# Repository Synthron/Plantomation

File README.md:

# Plantomation
Automatic Plant Watering System with ESP32

## V1
Capable of handling 4 channels simultaneously with one pump

## V2
Capable of handling 12 channels simultaneously with two pumps

---
**WORK IN PROGRESS**

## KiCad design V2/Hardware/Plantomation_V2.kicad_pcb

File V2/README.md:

# Plantomation

DIY plant watering system based on ESP32-S3-WROVER

## Features

- up to 12 channels simultaneously
- water spill detection
- Ambient Temperature and Humidity Sensor
- two pumps for all channels, selected via valves
  - Water pump
  - fertilizer pump
- simple Web-Interface for quick overview and configuration
- SD-Card for local wifi config and logging

## ToDos

- Documentation
  - [ ] Config Explanation
  - [ ] Wifi Management Explanation
  - [ ] UI Explanation
  - [ ] Control Modes Explanation
  - [ ] General Mode of Operation Explanation
- PCB
  - [x] Finish Design
  - [ ] Order
  - [ ] Assemble
  - [ ] Test
- Firmware
  - Frontend
    - [ ] Ajax working
    - [ ] Multi-Page working
    - [ ] Main-Page with all necessary information
    - [ ] Config page
    - [ ] About page
  - Backend
    - [ ] Wifi Management
    - [ ] File Management
      - [ ] SPIFFS
      - [ ] SD Card (preferred if available)
      - [ ] Copy config from SD to SPIFFS
    - [ ] Implement Setup via Webpage
      - [ ] Channels
      - [ ] WiFi
      - [ ] General Config
      - [ ] Debug
      - [ ] Sensor calibration
    - [ ] Objects for channels
    - [ ] Config object
    - [ ] Wifi object
    - [ ] implement sensor read
    - [ ] implement spill detection
    - [ ] implement Moisture Control
    - [ ] implement Time Control (timers)
    - [ ] implement internal water volume counter
    - [ ] implement low-water-alarm
    - [ ] Debug-Levels
    - [ ] Log-Levels

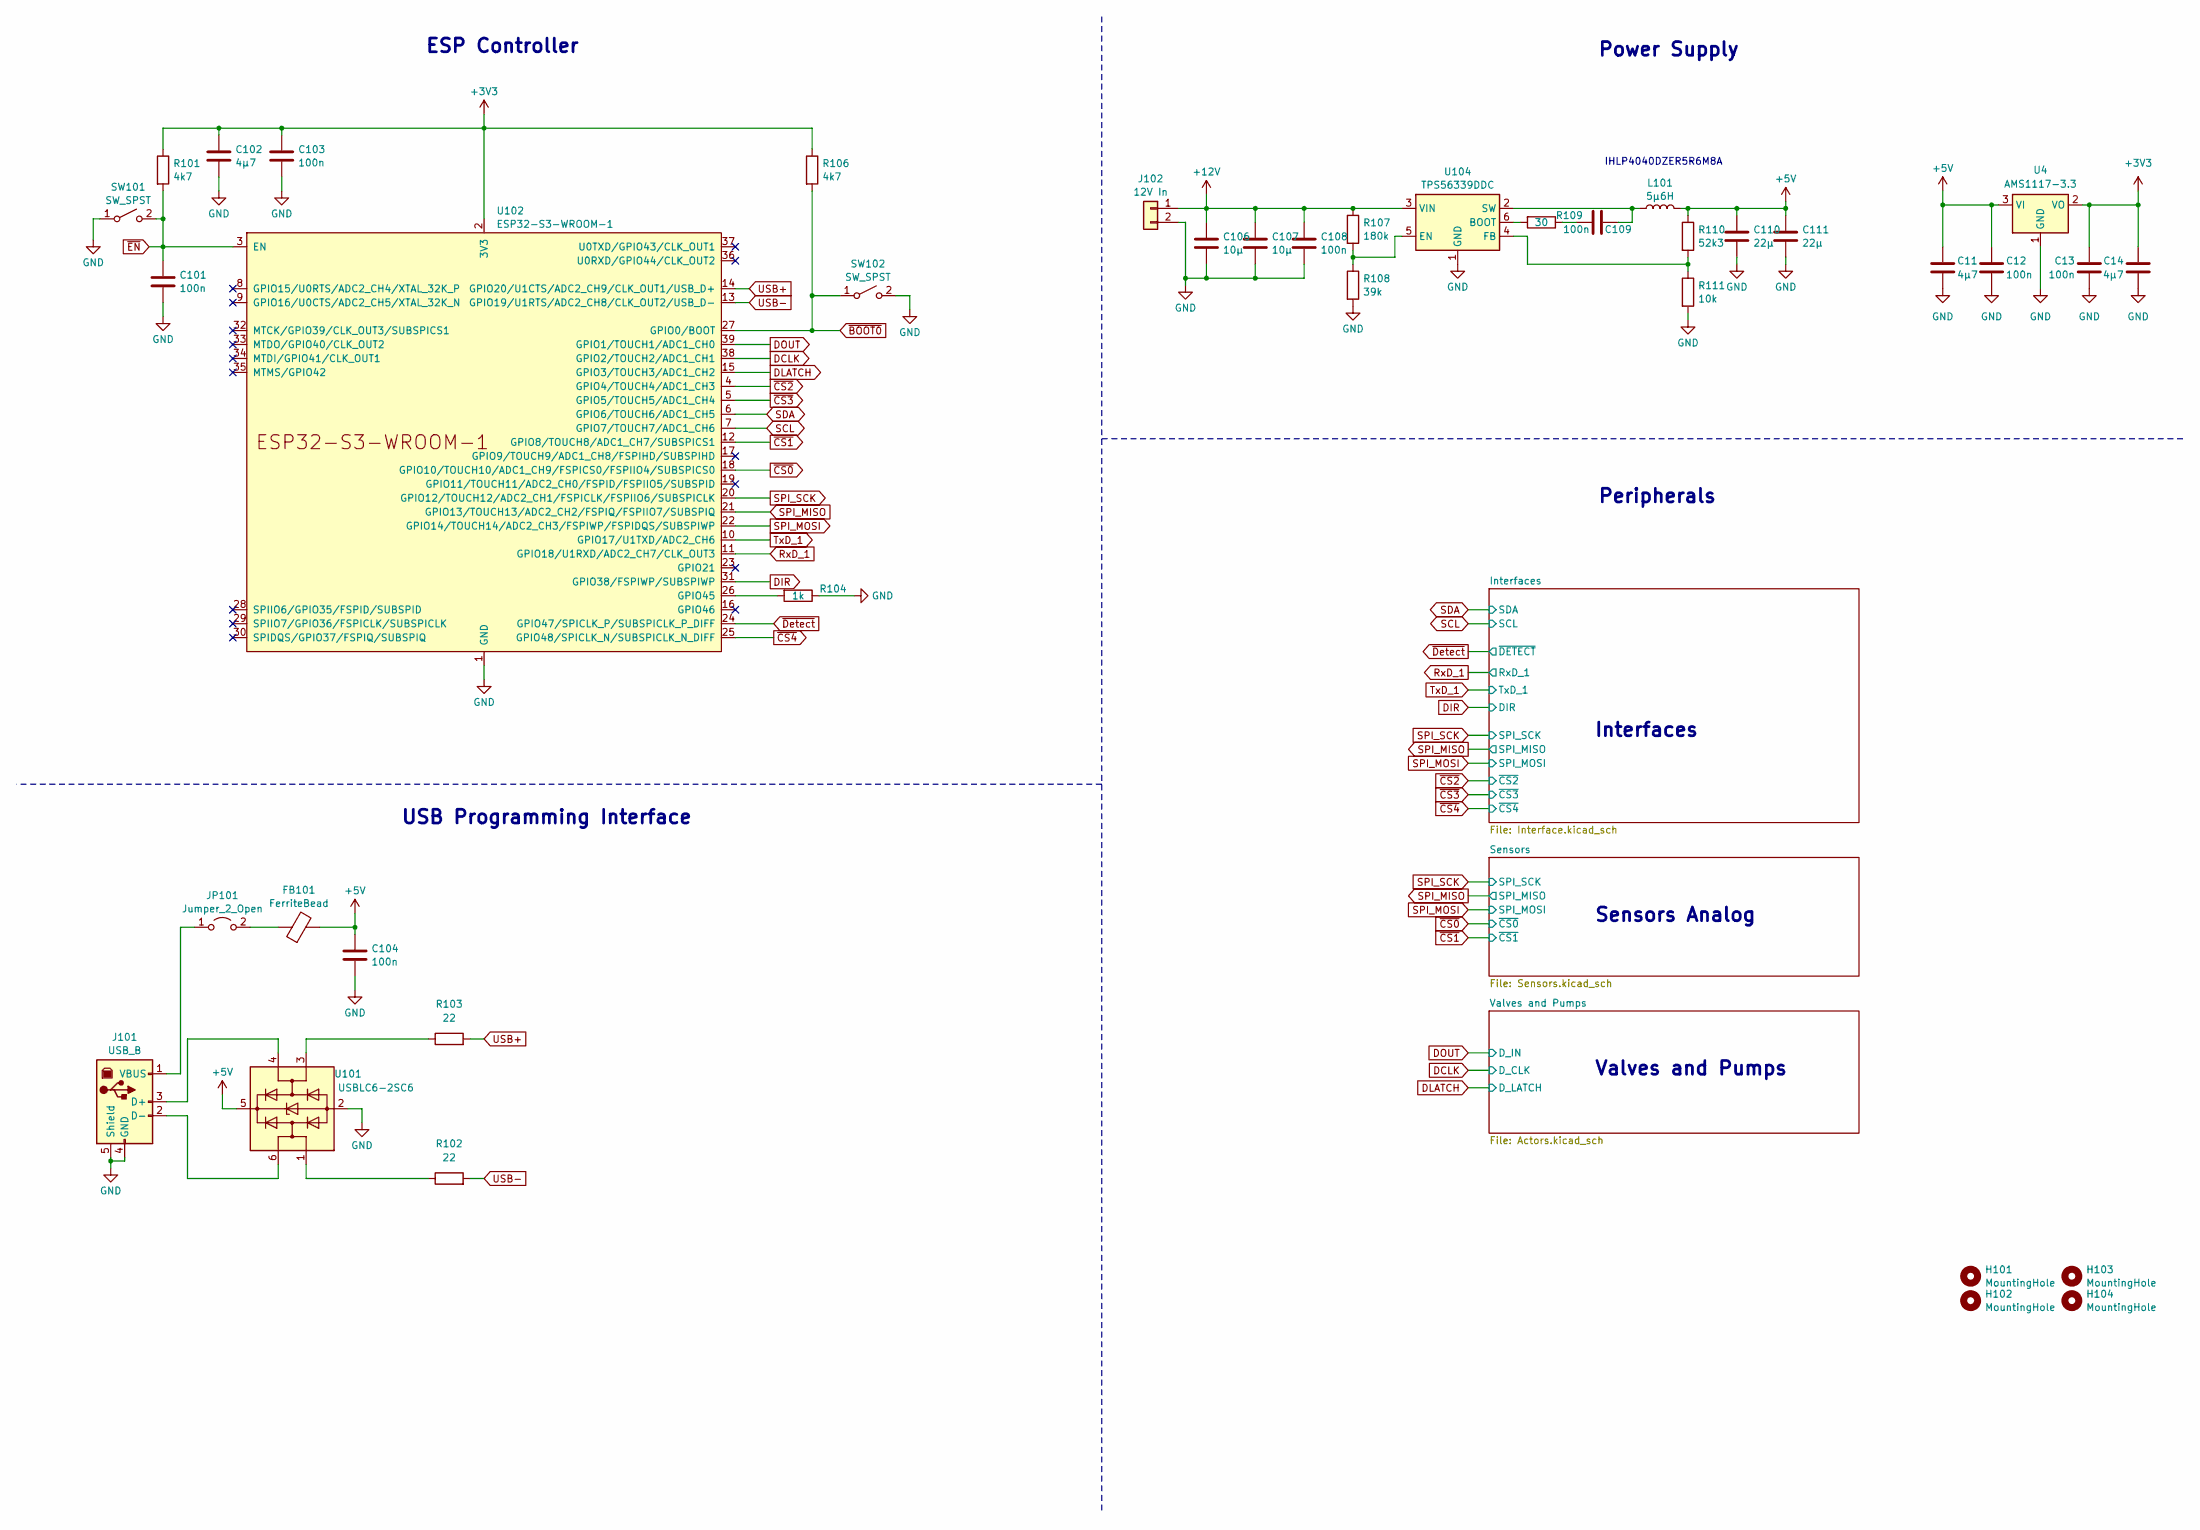
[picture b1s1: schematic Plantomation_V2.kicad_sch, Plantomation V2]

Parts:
C11, C14, C102: 4µ7; C_0805_2012Metric
C12, C13, C101, C103, C104, C108, C109: 100n; C_0805_2012Metric
C106, C107: 10µ; C_0805_2012Metric
C110, C111: 22µ; C_0805_2012Metric
FB101: FerriteBead; SMB-001
H101, H102, H103, H104: MountingHole; MountingHole_3.2mm_M3
J101: USB_B; USB_B_Lumberg_2411_02_Horizontal
J102: 12V In; JST_XH_B2B-XH-A_1x02_P2.50mm_Vertical
JP101: Jumper_2_Open; SolderJumper-2_P1.3mm_Open_TrianglePad1.0x1.5mm
L101: 5µ6H; L_Vishay_IHLP-4040
R101, R106: 4k7; R_0805_2012Metric
R102, R103: 22; R_0805_2012Metric
R104: 1k; R_0805_2012Metric
R107: 180k; R_0805_2012Metric
R108: 39k; R_0805_2012Metric
R109: 30; R_0805_2012Metric
R110: 52k3; R_0805_2012Metric
R111: 10k; R_0805_2012Metric
SW101, SW102: SW_SPST; SW_Tactile_SPST_NO_Straight_CK_PTS636Sx25SMTRLFS
U4: AMS1117-3.3; SOT-223-3_TabPin2
U101: USBLC6-2SC6; SOT-23-6
U102: ESP32-S3-WROOM-1
U104: TPS56339DDC; SOT-23-6

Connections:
+3V3: C102.1, C103.1, R101.1, R106.1, U102.2 (3V3); also elsewhere on the board
+5V: C104.1, C110.1, C111.1, FB101.2, L101.2, R110.1, U101.5 (VBUS); also elsewhere on the board
+12V: C106.1, C107.1, C108.1, J102.1, R107.1, U104.3 (VIN); also elsewhere on the board
DCLK: U102.38 (GPIO2/TOUCH2/ADC1_CH1); also elsewhere on the board
DIR: U102.31 (GPIO38/FSPIWP/SUBSPIWP)
DLATCH: U102.15 (GPIO3/TOUCH3/ADC1_CH2); also elsewhere on the board
DOUT: U102.39 (GPIO1/TOUCH1/ADC1_CH0); also elsewhere on the board
GND: C101.2, C102.2, C103.2, C104.2, C106.2, C107.2, C108.2, C110.2, C111.2, J101.4 (GND), J101.5 (Shield), J102.2, R104.1, R108.2, R111.2, SW101.1 (A), SW102.2 (B), U101.2 (GND), U102.1 (GND), U102.40 (GND), U102.41 (GND), U104.1 (GND); also elsewhere on the board
unnamed: C109.1, R109.1
unnamed: J101.3 (D+), U101.4 (I/O2)
unnamed: J101.2 (D-), U101.6 (I/O1)
unnamed: J101.1 (VBUS), JP101.1 (A)
unnamed: FB101.1, JP101.2 (B)
unnamed: R102.1, U101.1 (I/O1)
unnamed: R103.1, U101.3 (I/O2)
unnamed: R104.2, U102.26 (GPIO45)
unnamed: R109.2, U104.6 (BOOT)
unnamed: R107.2, R108.1, U104.5 (EN)
unnamed: R110.2, R111.1, U104.4 (FB)
unnamed: C109.2, L101.1, U104.2 (SW)
RxD_1: U102.11 (GPIO18/U1RXD/ADC2_CH7/CLK_OUT3)
SCL: U102.7 (GPIO7/TOUCH7/ADC1_CH6); also elsewhere on the board
SDA: U102.6 (GPIO6/TOUCH6/ADC1_CH5); also elsewhere on the board
SPI_MISO: U102.21 (GPIO13/TOUCH13/ADC2_CH2/FSPIQ/FSPIIO7/S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); also elsewhere on the board
SPI_MOSI: U102.22 (GPIO14/TOUCH14/ADC2_CH3/FSPIWP/FSPIDQS/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); also elsewhere on the board
SPI_SCK: U102.20 (GPIO12/TOUCH12/ADC2_CH1/FSPICLK/FSPIIO6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); also elsewhere on the board
TxD_1: U102.10 (GPIO17/U1TXD/ADC2_CH6)
USB+: R103.2, U102.14 (GPIO20/U1CTS/ADC2_CH9/CLK_OUT1/USB_D+)
USB-: R102.2, U102.13 (GPIO19/U1RTS/ADC2_CH8/CLK_OUT2/USB_D-)
~BOOT0: R106.2, SW102.1 (A), U102.27 (GPIO0/BOOT)
~CS0: U102.18 (GPIO10/TOUCH10/ADC1_CH9/FSPICS0/FSPIIO4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); also elsewhere on the board
~CS1: U102.12 (GPIO8/TOUCH8/ADC1_CH7/SUBSPICS1); also elsewhere on the board
~CS2: U102.4 (GPIO4/TOUCH4/ADC1_CH3); also elsewhere on the board
~CS3: U102.5 (GPIO5/TOUCH5/ADC1_CH4); also elsewhere on the board
~CS4: U102.25 (GPIO48/SPICLK_N/SUBSPICLK_N_DIFF); also elsewhere on the board
~Detect: U102.24 (GPIO47/SPICLK_P/SUBSPICLK_P_DIFF); also elsewhere on the board
~EN: C101.1, R101.2, SW101.2 (B), U102.3 (EN)

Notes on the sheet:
Valves and Pumps
IHLP4040DZER5R6M8A
Interfaces
Sensors Analog
Peripherals
Power Supply
ESP Controller
USB Programming Interface

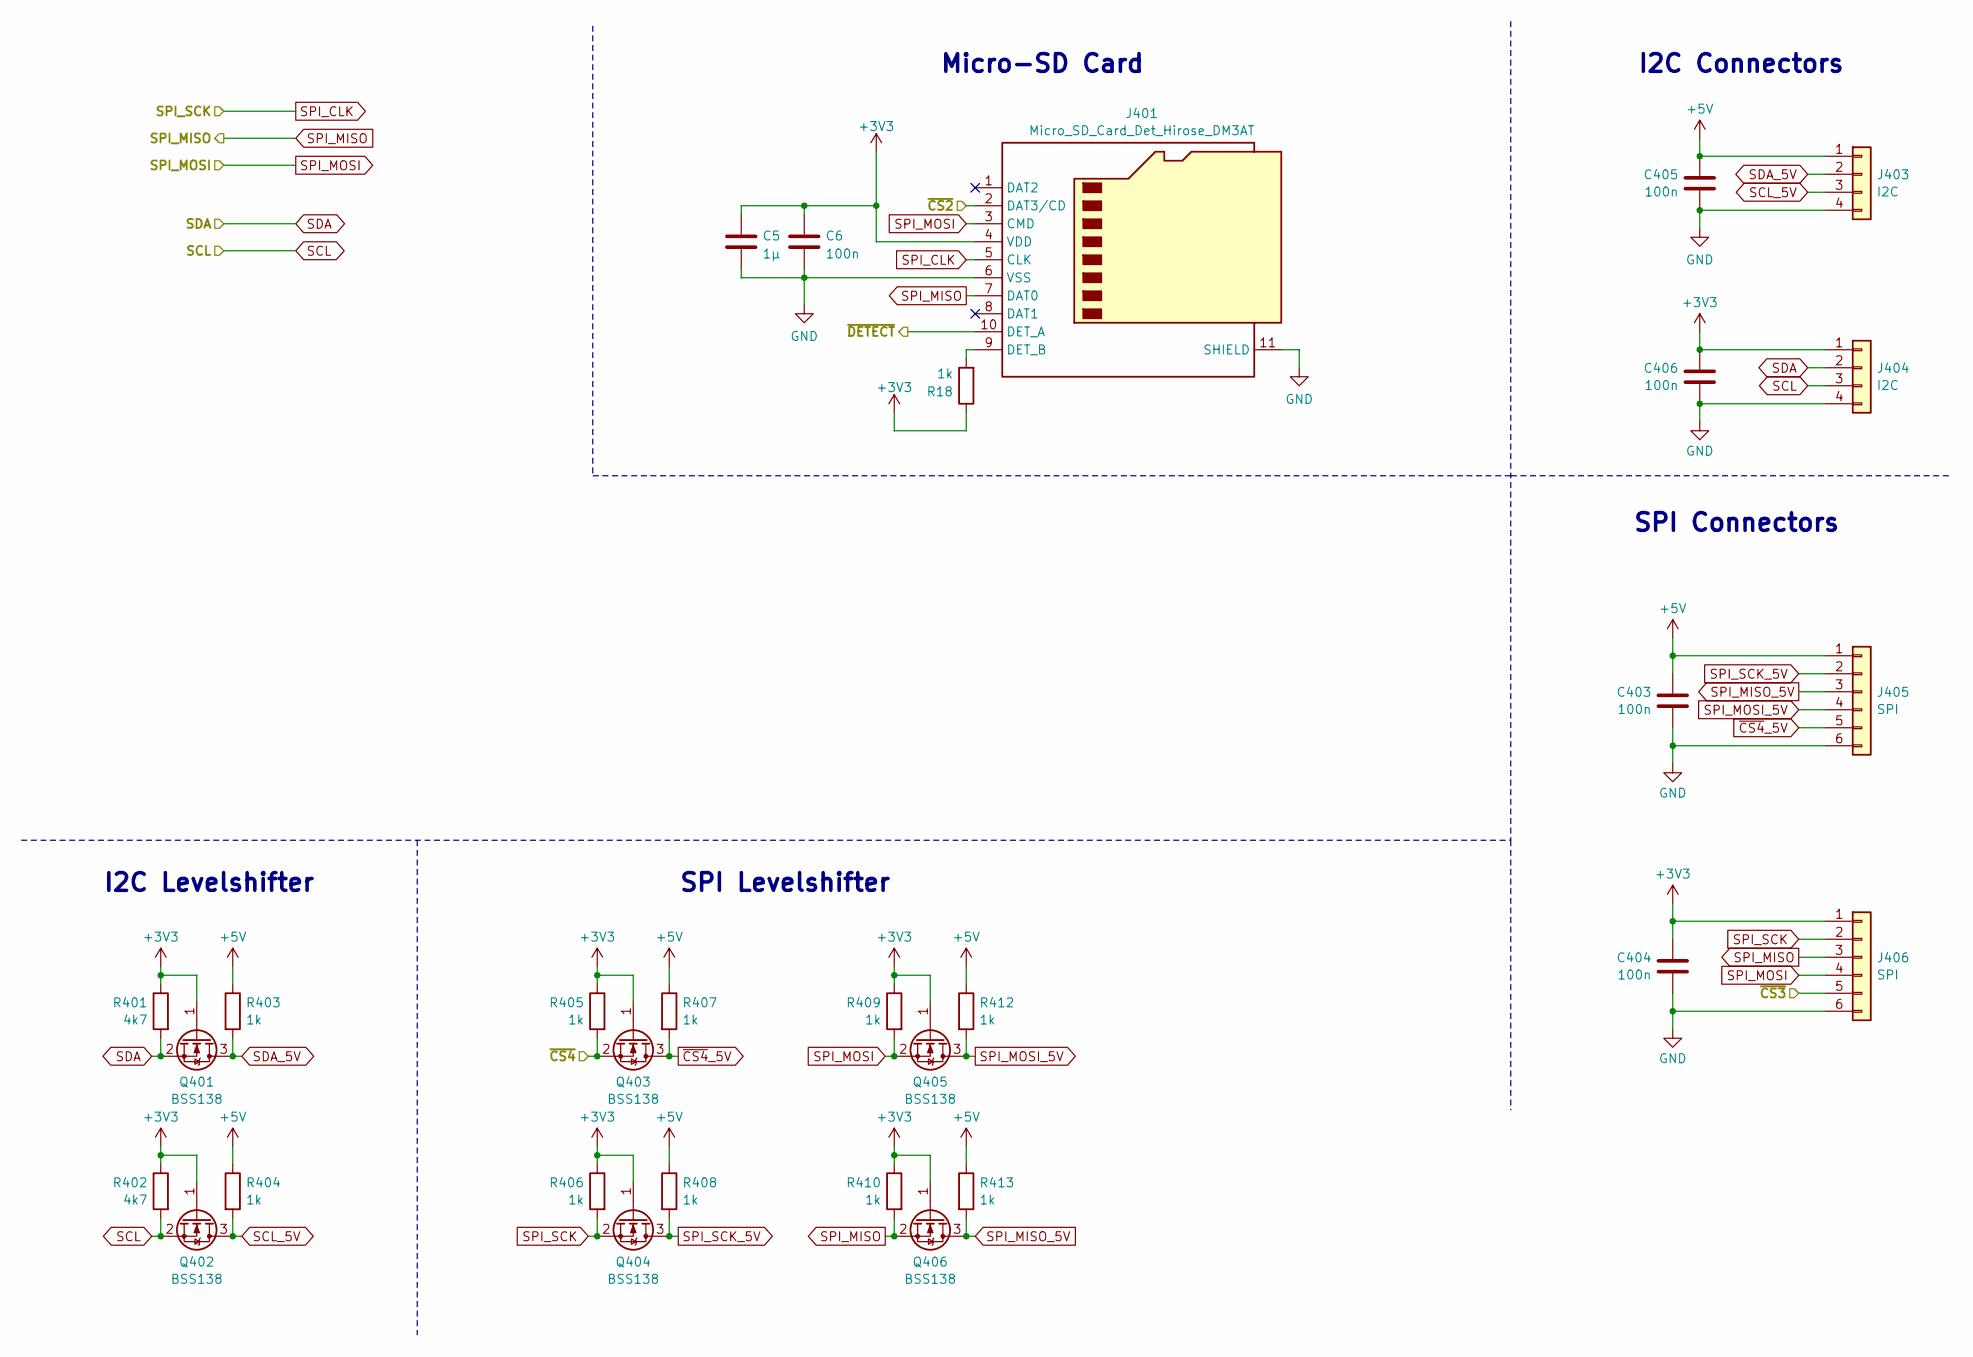
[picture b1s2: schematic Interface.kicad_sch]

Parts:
C5: 1µ; C_0805_2012Metric
C6, C403, C404, C405, C406: 100n; C_0805_2012Metric
J401: Micro_SD_Card_Det_Hirose_DM3AT; microSD_HC_Hirose_DM3AT-SF-PEJM5
J403, J404: I2C; PinHeader_1x04_P2.54mm_Vertical
J405, J406: SPI; PinHeader_1x06_P2.54mm_Vertical
Q401, Q402, Q403, Q404, Q405, Q406: BSS138; SOT-23
R18, R403, R404, R405, R406, R407, R408, R409, R410, R412, R413: 1k; R_0805_2012Metric
R401, R402: 4k7; R_0805_2012Metric

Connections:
+3V3: C404.1, C406.1, J401.4 (VDD), J404.1, J406.1, Q401.1 (G), Q402.1 (G), Q403.1 (G), Q404.1 (G), Q405.1 (G), Q406.1 (G), R401.1, R402.1, R405.1, R406.1, R409.1, R410.1; also elsewhere on the board
+5V: C403.1, C405.1, J403.1, J405.1, R403.1, R404.1, R407.1, R408.1, R412.1, R413.1; also elsewhere on the board
GND: C403.2, C404.2, C405.2, C406.2, J401.6 (VSS), J401.11 (SHIELD), J403.4, J404.4, J405.6, J406.6; also elsewhere on the board
unnamed 51: J401.9 (DET_B); also elsewhere on the board
SCL: J404.3, Q402.2 (S), R402.2; also elsewhere on the board
SCL_5V: J403.3, Q402.3 (D), R404.2
SDA: J404.2, Q401.2 (S), R401.2; also elsewhere on the board
SDA_5V: J403.2, Q401.3 (D), R403.2
SPI_MISO: J401.7 (DAT0), J406.3, Q406.2 (S), R410.2; also elsewhere on the board
SPI_MISO_5V: J405.3, Q406.3 (D), R413.2
SPI_MOSI: J401.3 (CMD), J406.4, Q405.2 (S), R409.2; also elsewhere on the board
SPI_MOSI_5V: J405.4, Q405.3 (D), R412.2
SPI_SCK: J401.5 (CLK), J406.2, Q404.2 (S), R406.2; also elsewhere on the board
SPI_SCK_5V: J405.2, Q404.3 (D), R408.2
~CS2: J401.2 (DAT3/CD); also elsewhere on the board
~CS3: J406.5; also elsewhere on the board
~CS4: Q403.2 (S), R405.2; also elsewhere on the board
~CS4_5V: J405.5, Q403.3 (D), R407.2
~Detect: J401.10 (DET_A); also elsewhere on the board

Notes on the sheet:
I2C Connectors
SPI Levelshifter
Micro-SD Card
SPI Connectors
I2C Levelshifter

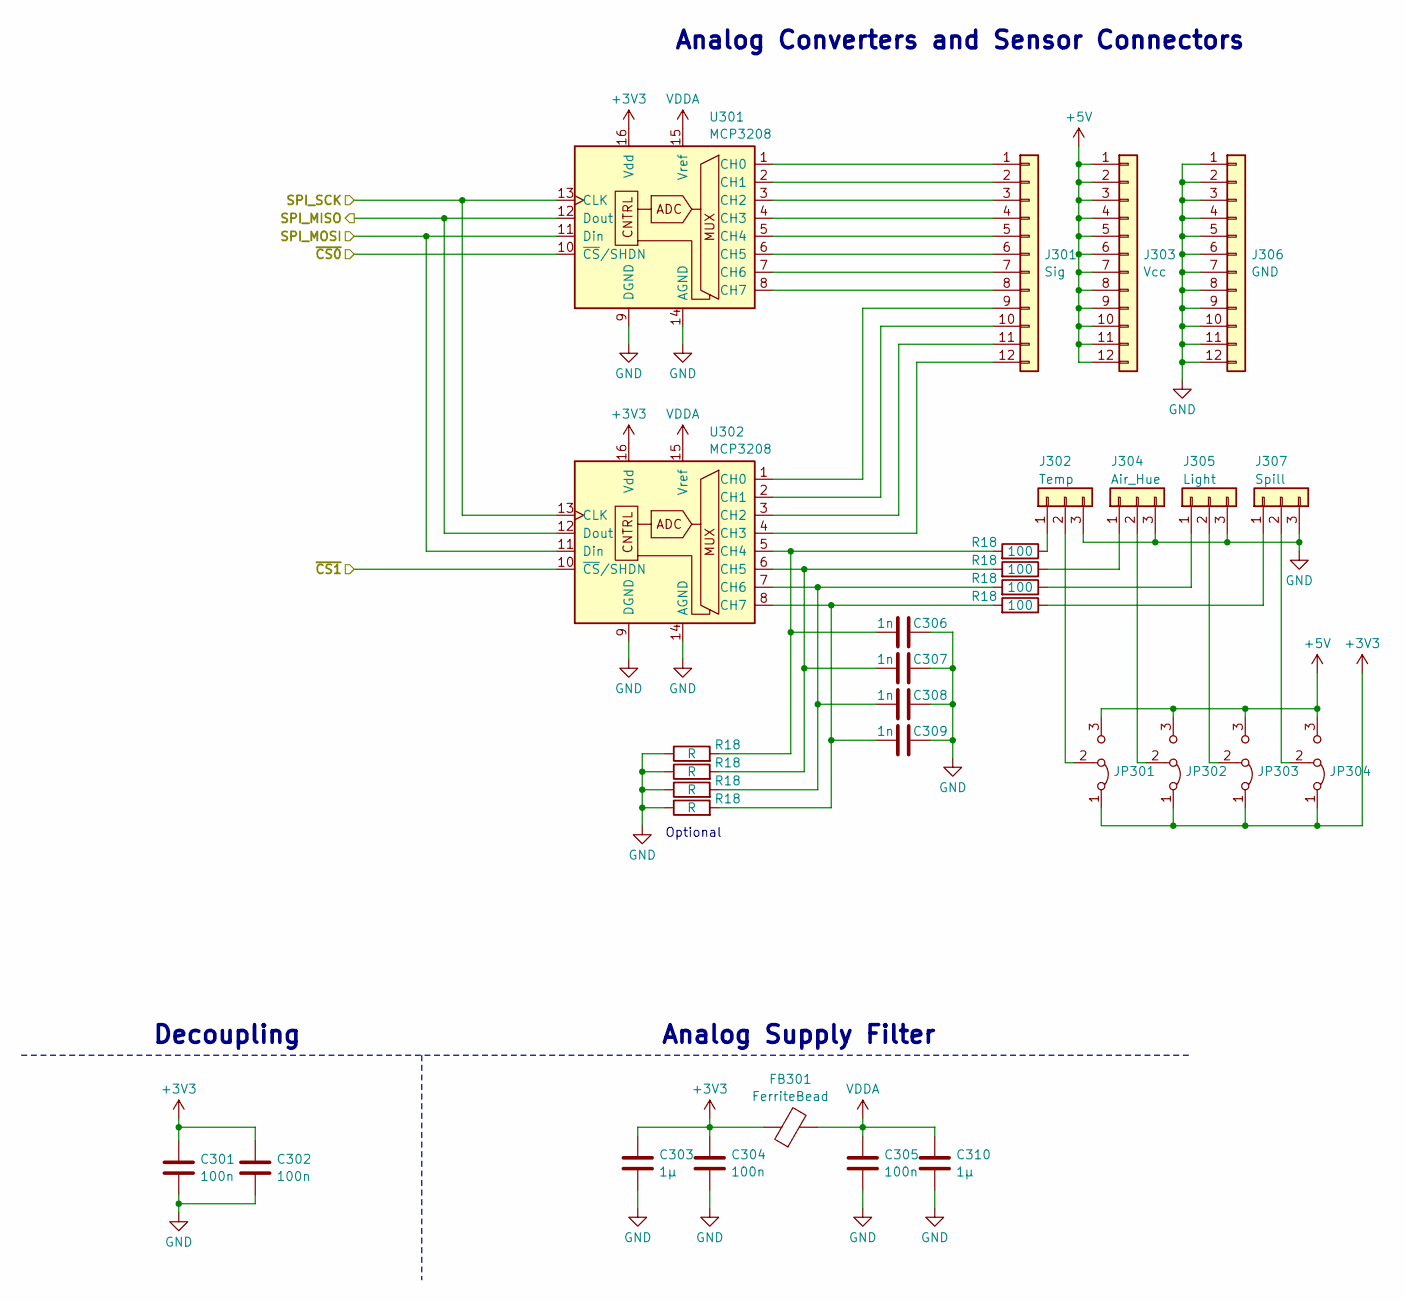
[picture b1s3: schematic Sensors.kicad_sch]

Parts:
C301, C302, C304, C305: 100n; C_0805_2012Metric
C303, C310: 1µ; C_0805_2012Metric
C306, C307, C308, C309: 1n; C_0805_2012Metric
FB301: FerriteBead; SMB-001
J301: Sig; PinHeader_1x12_P2.54mm_Vertical
J302: Temp; PinHeader_1x03_P2.54mm_Vertical
J303: Vcc; PinHeader_1x12_P2.54mm_Vertical
J304: Air_Hue; PinHeader_1x03_P2.54mm_Vertical
J305: Light; PinHeader_1x03_P2.54mm_Vertical
J306: GND; PinHeader_1x12_P2.54mm_Vertical
J307: Spill; PinHeader_1x03_P2.54mm_Vertical
JP301, JP302, JP303, JP304: Jumper_3_Bridged12; SolderJumper-3_P1.3mm_Open_Pad1.0x1.5mm
R18: R; R_0805_2012Metric
U301, U302: MCP3208; SOIC-16_4.55x10.3mm_P1.27mm

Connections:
+3V3: C301.1, C302.1, C303.1, C304.1, FB301.1, JP301.1 (A), JP302.1 (A), JP303.1 (A), JP304.1 (A), U301.16 (Vdd), U302.16 (Vdd); also elsewhere on the board
+5V: J303.1, J303.2, J303.3, J303.4, J303.5, J303.6, J303.7, J303.8, J303.9, J303.10, J303.11, J303.12, JP301.3 (B), JP302.3 (B), JP303.3 (B), JP304.3 (B); also elsewhere on the board
GND: C301.2, C302.2, C303.2, C304.2, C305.2, C306.2, C307.2, C308.2, C309.2, C310.2, J302.3, J304.3, J305.3, J306.1, J306.2, J306.3, J306.4, J306.5, J306.6, J306.7, J306.8, J306.9, J306.10, J306.11, J306.12, J307.3, U301.9 (DGND), U301.14 (AGND), U302.9 (DGND), U302.14 (AGND); also elsewhere on the board
unnamed: J301.1, U301.1 (CH0)
unnamed: J301.2, U301.2 (CH1)
unnamed: J301.3, U301.3 (CH2)
unnamed: J301.4, U301.4 (CH3)
unnamed: J301.5, U301.5 (CH4)
unnamed: J301.6, U301.6 (CH5)
unnamed: J301.7, U301.7 (CH6)
unnamed: J301.8, U301.8 (CH7)
unnamed: J301.9, U302.1 (CH0)
unnamed: J301.10, U302.2 (CH1)
unnamed: J301.11, U302.3 (CH2)
unnamed: J301.12, U302.4 (CH3)
unnamed 43: J302.1; also elsewhere on the board
unnamed: J302.2, JP301.2 (C)
unnamed 45: J304.1; also elsewhere on the board
unnamed: J304.2, JP302.2 (C)
unnamed 47: J305.1; also elsewhere on the board
unnamed: J305.2, JP303.2 (C)
unnamed 49: J307.1; also elsewhere on the board
unnamed: J307.2, JP304.2 (C)
unnamed 75: C306.1, U302.5 (CH4); also elsewhere on the board
unnamed 76: C307.1, U302.6 (CH5); also elsewhere on the board
unnamed 77: C308.1, U302.7 (CH6); also elsewhere on the board
unnamed 78: C309.1, U302.8 (CH7); also elsewhere on the board
SPI_MISO: U301.12 (Dout), U302.12 (Dout); also elsewhere on the board
SPI_MOSI: U301.11 (Din), U302.11 (Din); also elsewhere on the board
SPI_SCK: U301.13 (CLK), U302.13 (CLK); also elsewhere on the board
VDDA: C305.1, C310.1, FB301.2, U301.15 (Vref), U302.15 (Vref)
~CS0: U301.10 (~CS/SHDN); also elsewhere on the board
~CS1: U302.10 (~CS/SHDN); also elsewhere on the board

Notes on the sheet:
Analog Converters and Sensor Connectors
Analog Supply Filter
Decoupling
Optional

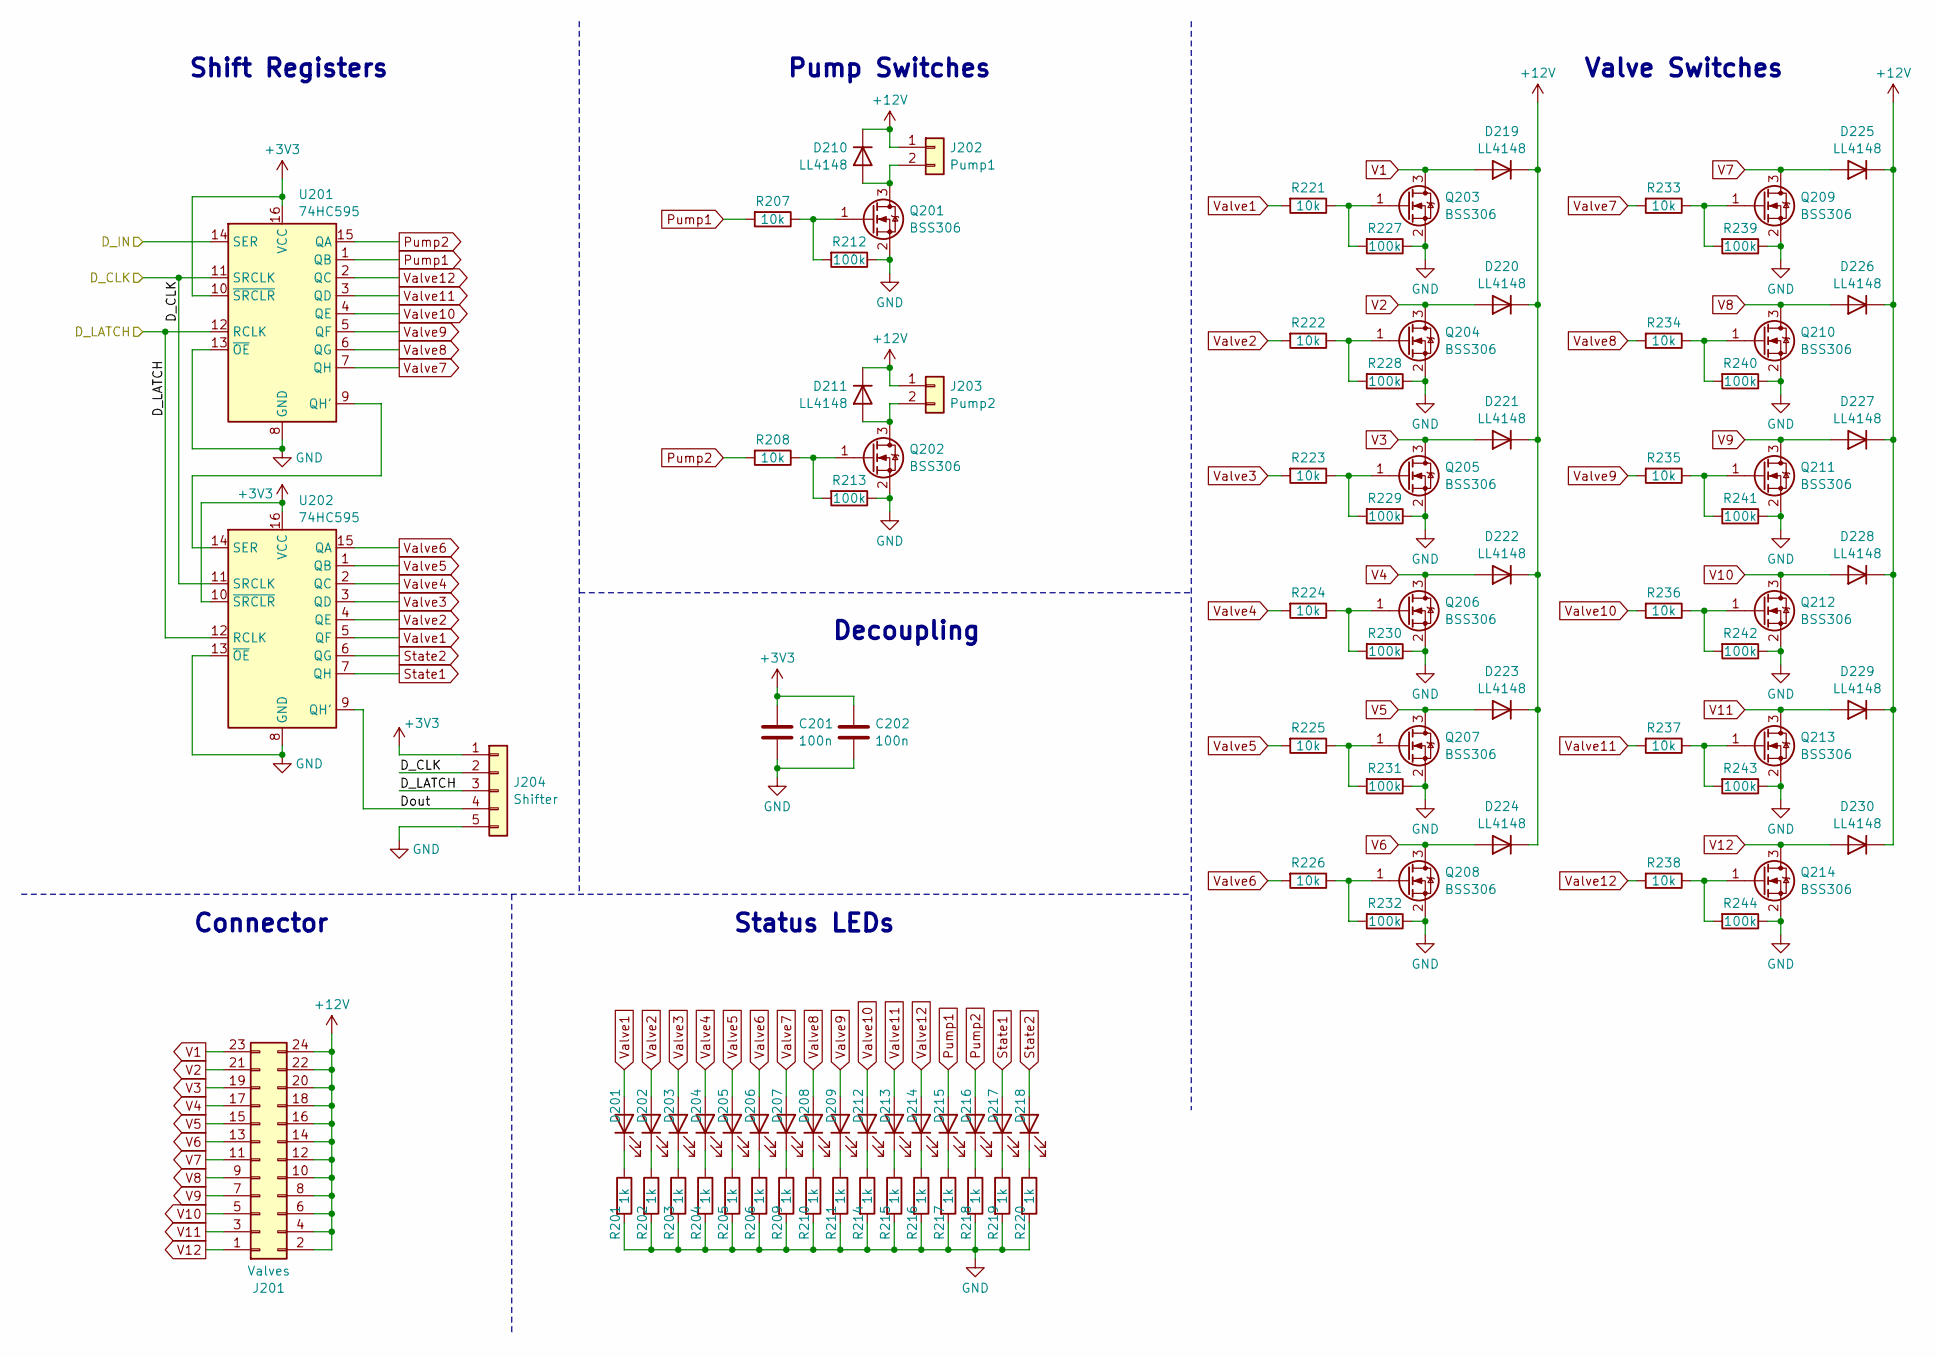
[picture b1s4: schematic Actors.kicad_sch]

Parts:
C201, C202: 100n; C_0805_2012Metric
D201, D202, D203, D204, D205, D206, D207, D208, D209, D212, D213, D214, D215, D216, D217, D218: LED; LED_0805_2012Metric
D210, D211, D219, D220, D221, D222, D223, D224, D225, D226, D227, D228, D229, D230: LL4148; D_MiniMELF
J201: Valves; PinHeader_2x12_P2.54mm_Vertical
J202: Pump1; JST_XH_B2B-XH-A_1x02_P2.50mm_Vertical
J203: Pump2; JST_XH_B2B-XH-A_1x02_P2.50mm_Vertical
J204: Shifter; PinSocket_1x05_P2.54mm_Vertical
Q201, Q202, Q203, Q204, Q205, Q206, Q207, Q208, Q209, Q210, Q211, Q212, Q213, Q214: BSS306; SOT-23-3
R201, R202, R203, R204, R205, R206, R209, R210, R211, R214, R215, R216, R217, R218, R219, R220: 1k; R_0805_2012Metric
R207, R208, R221, R222, R223, R224, R225, R226, R233, R234, R235, R236, R237, R238: 10k; R_0805_2012Metric
R212, R213, R227, R228, R229, R230, R231, R232, R239, R240, R241, R242, R243, R244: 100k; R_0805_2012Metric
U201, U202: 74HC595; SOIC-16_4.55x10.3mm_P1.27mm

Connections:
+3V3: C201.1, C202.1, J204.1, U201.10 (~SRCLR), U201.16 (VCC), U202.10 (~SRCLR), U202.16 (VCC); also elsewhere on the board
+12V: D210.1 (K), D211.1 (K), D219.1 (K), D220.1 (K), D221.1 (K), D222.1 (K), D223.1 (K), D224.1 (K), D225.1 (K), D226.1 (K), D227.1 (K), D228.1 (K), D229.1 (K), D230.1 (K), J201.2, J201.4, J201.6, J201.8, J201.10, J201.12, J201.14, J201.16, J201.18, J201.20, J201.22, J201.24, J202.1, J203.1; also elsewhere on the board
/Valves and Pumps/Dout: J204.4, U202.9 (QH')
DCLK: J204.2, U201.11 (SRCLK), U202.11 (SRCLK); also elsewhere on the board
DLATCH: J204.3, U201.12 (RCLK), U202.12 (RCLK); also elsewhere on the board
DOUT: U201.14 (SER); also elsewhere on the board
GND: C201.2, C202.2, J204.5, Q201.2 (S), Q202.2 (S), Q203.2 (S), Q204.2 (S), Q205.2 (S), Q206.2 (S), Q207.2 (S), Q208.2 (S), Q209.2 (S), Q210.2 (S), Q211.2 (S), Q212.2 (S), Q213.2 (S), Q214.2 (S), R201.2, R202.2, R203.2, R204.2, R205.2, R206.2, R209.2, R210.2, R211.2, R212.1, R213.1, R214.2, R215.2, R216.2, R217.2, R218.2, R219.2, R220.2, R227.1, R228.1, R229.1, R230.1, R231.1, R232.1, R239.1, R240.1, R241.1, R242.1, R243.1, R244.1, U201.8 (GND), U201.13 (~OE), U202.8 (GND), U202.13 (~OE); also elsewhere on the board
unnamed: D201.1 (K), R201.1
unnamed: D202.1 (K), R202.1
unnamed: D203.1 (K), R203.1
unnamed: D204.1 (K), R204.1
unnamed: D205.1 (K), R205.1
unnamed: D206.1 (K), R206.1
unnamed: D207.1 (K), R209.1
unnamed: D208.1 (K), R210.1
unnamed: D209.1 (K), R211.1
unnamed: D210.2 (A), J202.2, Q201.3 (D)
unnamed: D211.2 (A), J203.2, Q202.3 (D)
unnamed: D212.1 (K), R214.1
unnamed: D213.1 (K), R215.1
unnamed: D214.1 (K), R216.1
unnamed: D215.1 (K), R217.1
unnamed: D216.1 (K), R218.1
unnamed: D217.1 (K), R219.1
unnamed: D218.1 (K), R220.1
unnamed: Q201.1 (G), R207.1, R212.2
unnamed: Q202.1 (G), R208.1, R213.2
unnamed: Q203.1 (G), R221.1, R227.2
unnamed: Q204.1 (G), R222.1, R228.2
unnamed: Q205.1 (G), R223.1, R229.2
unnamed: Q206.1 (G), R224.1, R230.2
unnamed: Q207.1 (G), R225.1, R231.2
unnamed: Q208.1 (G), R226.1, R232.2
unnamed: Q209.1 (G), R233.1, R239.2
unnamed: Q210.1 (G), R234.1, R240.2
unnamed: Q211.1 (G), R235.1, R241.2
unnamed: Q212.1 (G), R236.1, R242.2
unnamed: Q213.1 (G), R237.1, R243.2
unnamed: Q214.1 (G), R238.1, R244.2
unnamed: U201.9 (QH'), U202.14 (SER)
Pump1: D215.2 (A), R207.2, U201.1 (QB)
Pump2: D216.2 (A), R208.2, U201.15 (QA)
State1: D217.2 (A), U202.7 (QH)
State2: D218.2 (A), U202.6 (QG)
V1: D219.2 (A), J201.23, Q203.3 (D)
V2: D220.2 (A), J201.21, Q204.3 (D)
V3: D221.2 (A), J201.19, Q205.3 (D)
V4: D222.2 (A), J201.17, Q206.3 (D)
V5: D223.2 (A), J201.15, Q207.3 (D)
V6: D224.2 (A), J201.13, Q208.3 (D)
V7: D225.2 (A), J201.11, Q209.3 (D)
V8: D226.2 (A), J201.9, Q210.3 (D)
V9: D227.2 (A), J201.7, Q211.3 (D)
V10: D228.2 (A), J201.5, Q212.3 (D)
V11: D229.2 (A), J201.3, Q213.3 (D)
V12: D230.2 (A), J201.1, Q214.3 (D)
Valve1: D201.2 (A), R221.2, U202.5 (QF)
Valve2: D202.2 (A), R222.2, U202.4 (QE)
Valve3: D203.2 (A), R223.2, U202.3 (QD)
Valve4: D204.2 (A), R224.2, U202.2 (QC)
Valve5: D205.2 (A), R225.2, U202.1 (QB)
Valve6: D206.2 (A), R226.2, U202.15 (QA)
Valve7: D207.2 (A), R233.2, U201.7 (QH)
Valve8: D208.2 (A), R234.2, U201.6 (QG)
Valve9: D209.2 (A), R235.2, U201.5 (QF)
Valve10: D212.2 (A), R236.2, U201.4 (QE)
Valve11: D213.2 (A), R237.2, U201.3 (QD)
Valve12: D214.2 (A), R238.2, U201.2 (QC)

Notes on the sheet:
Valve Switches
Connector
Pump Switches
Status LEDs
Shift Registers
Decoupling

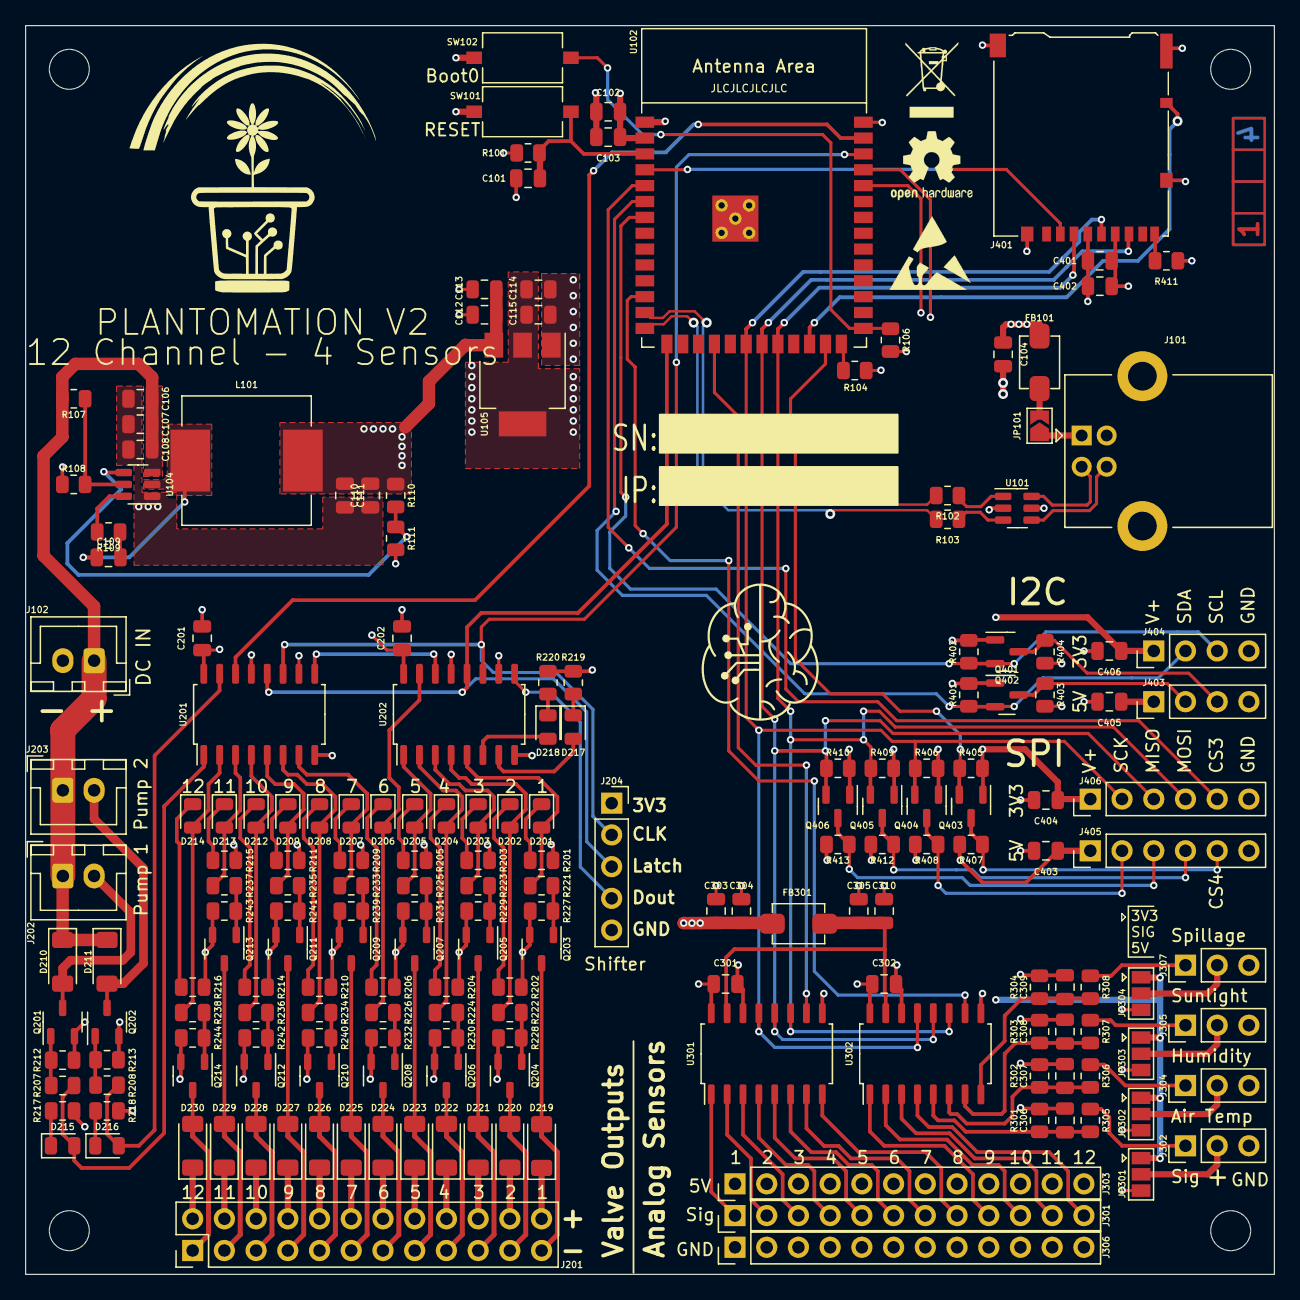
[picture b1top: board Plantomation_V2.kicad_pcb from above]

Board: 4 copper layers, 100.0 x 100.0 mm, 198 parts (0 on the bottom side), 128 nets.

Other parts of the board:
C112, C115: 4µ7; C_0805_2012Metric
C113, C114, C402: 100n; C_0805_2012Metric
C401: 1µ; C_0805_2012Metric
R301, R302, R303, R304: R; R_0805_2012Metric
R305, R306, R307, R308: 100; R_0805_2012Metric
R411: 1k; R_0805_2012Metric
Ref**: Val**; ladder_4
U105: AMS1117-3.3; SOT-223-3_TabPin2

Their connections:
+3V3: C114.1, C115.1, C401.1, C402.1, R411.1, U105.2 (VO); also elsewhere on the board
+5V: C112.1, C113.1, U105.3 (VI); also elsewhere on the board
GND: C112.2, C113.2, C114.2, C115.2, C401.2, C402.2, R301.1, R302.1, R303.1, R304.1, U105.1 (GND); also elsewhere on the board
unnamed 43: R305.1; also elsewhere on the board
unnamed 45: R306.1; also elsewhere on the board
unnamed 47: R307.1; also elsewhere on the board
unnamed 49: R308.1; also elsewhere on the board
unnamed 51: R411.2; also elsewhere on the board
unnamed 75: R301.2, R305.2; also elsewhere on the board
unnamed 76: R302.2, R306.2; also elsewhere on the board
unnamed 77: R303.2, R307.2; also elsewhere on the board
unnamed 78: R304.2, R308.2; also elsewhere on the board
